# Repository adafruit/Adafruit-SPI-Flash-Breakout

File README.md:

## Adafruit SPI Flash Breakouts

&nbsp; 
<br />
&nbsp; 

Click to purchase from the Adafruit Shop:
- [Adafruit SPI FLASH Breakout - W25Q16 - 16 Mbit / 2 MByte](https://www.adafruit.com/product/5635)
- [Adafruit SPI FLASH Breakout - W25Q64 - 64 MBit / 8 MByte](https://www.adafruit.com/product/5636)
- [Adafruit SPI FLASH Breakout W25Q128 - 128 MBit / 16 MByte](https://www.adafruit.com/product/5643)

PCB files for the Adafruit SPI Flash Breakouts. 

Format is EagleCAD schematic and board layout

### Description

Sometimes you need a little extra storage for your microcontroller projects: for files, images, fonts, audio clips, etc. If you need lots of space, like in the gigabytes, we always recommend an SD card because you can easily plug it into a computer to edit files. But sometimes you don't need whole gigabytes, you just need a megabyte or two, with the lower cost and power usage that comes with it. That's when we recommend an Adafruit SPI FLASH Breakout such as this one that is fitted with a W25Q16 - 16 Mbit / 2 MByte, W25Q64 - 64 Mbit / 8 MByte or W25Q128 - 128 Mbit / 16 MByte chip.

Compared to our QSPI breakouts, this one is single-channel SPI only...BUT it comes with level shifting so it can be used safely with 3V or 5V power and logic. Since we needed to add level shifting, the chip is pre-wired into single channel "SPI" mode, with a level shifters so you can use it with 3V or 5V logic easily. You also get a 3.3V regulator and a pullup on CS. 

Note that the chips come blank, and do not have a wear-leveling subsystem. You can address them as a flat memory space or, if you like, format them with a filesystem like littleFS or FAT. Great for use with data-logging or storage needs where you are OK with doing the management yourself - or if you are adding external memory to an older chip that would like 5V-compatibility.

In Arduino, we have the Adafruit_SPIFlash library that can be used to interface with this chip. Comes with a bit of header that can be used to solder in and plug into a breadboard if desired.

### License

Adafruit invests time and resources providing this open source design, please support Adafruit and open-source hardware by purchasing products from [Adafruit](https://www.adafruit.com)!

Designed by Limor Fried/Ladyada for Adafruit Industries.

Creative Commons Attribution/Share-Alike, all text above must be included in any redistribution. 
See license.txt for additional details.

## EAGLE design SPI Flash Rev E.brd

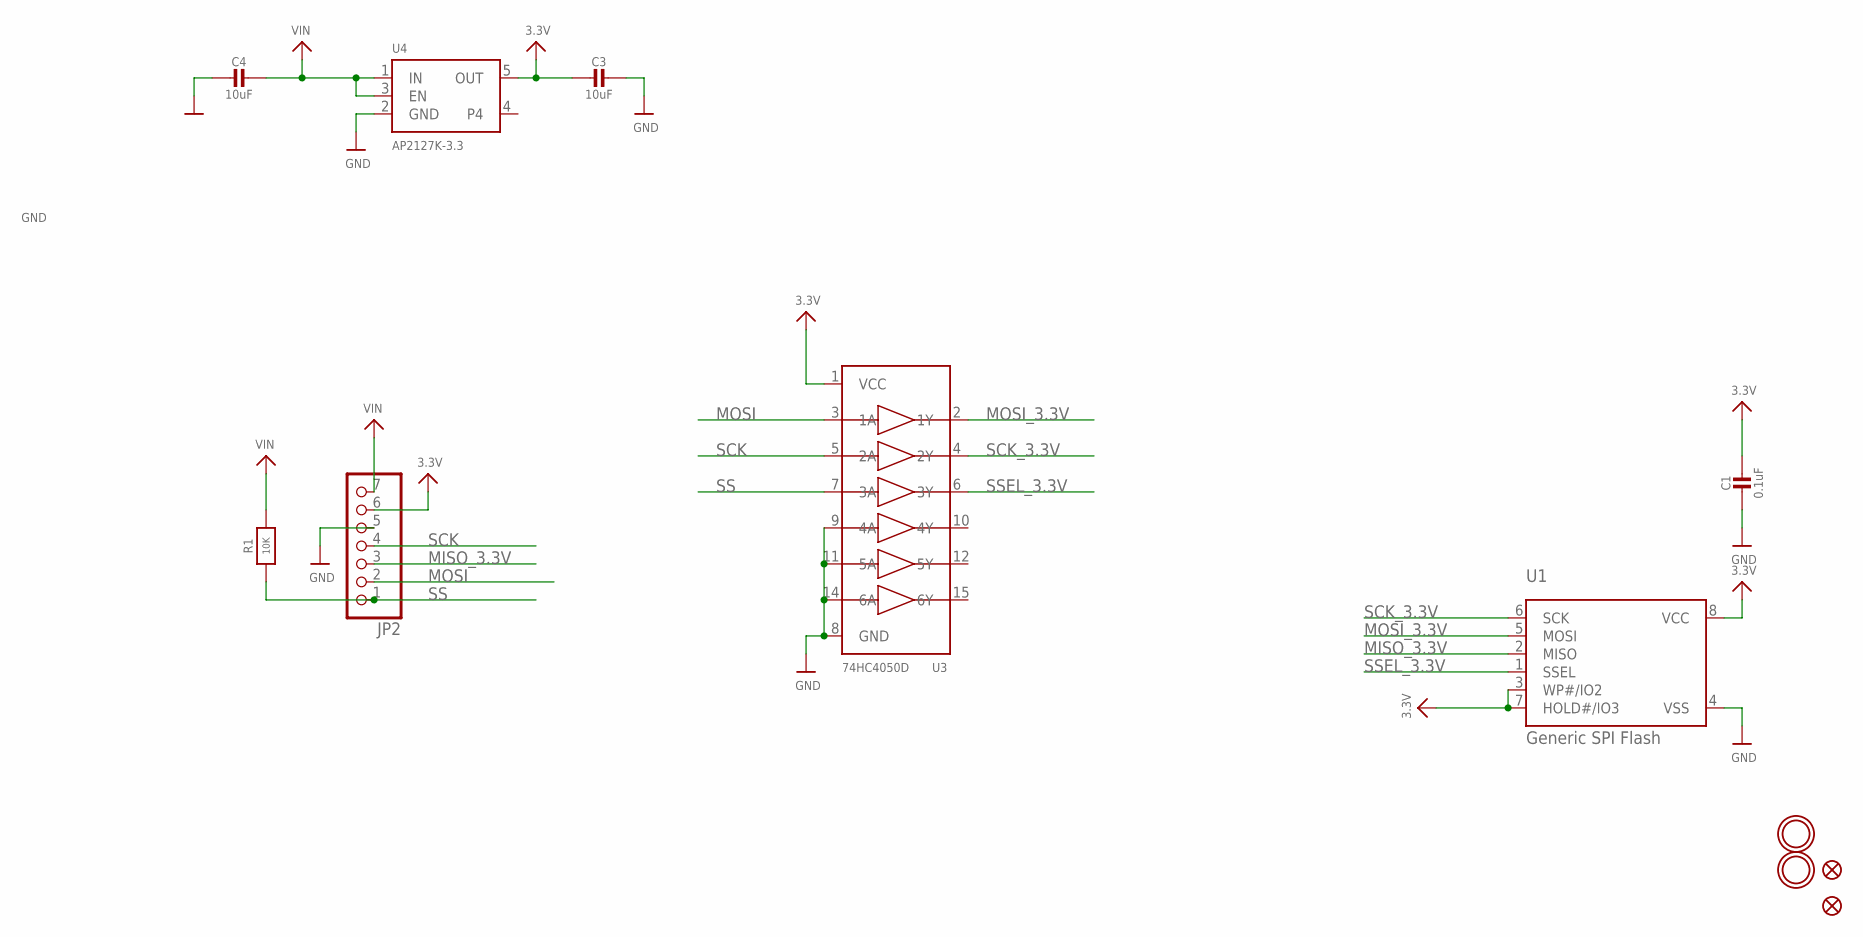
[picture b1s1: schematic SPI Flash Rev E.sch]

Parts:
C1: 0.1uF; 0603-NO
C3, C4: 10uF; 0805-NO
FID2, FID3: FIDUCIAL_1MM
JP2: HEADER-1X770MIL; 1X07_ROUND_70
R1: 10K; 0603-NO
U1: Generic SPI Flash; SOIC8_208MIL
U3: 74HC4050D; TSSOP16
U4: AP2127K-3.3; SOT23-5
U$16, U$17: MOUNTINGHOLE2.5; MOUNTINGHOLE_2.5_PLATED

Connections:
3.3V: C1.1, C3.2, JP2.6, U1.3 (WP#/IO2), U1.7 (HOLD#/IO3), U1.8 (VCC), U3.1 (VCC), U4.5 (OUT)
GND: C1.2, C3.1, C4.2, JP2.5, U1.4 (VSS), U3.8 (GND), U3.9 (4A), U3.11 (5A), U3.14 (6A), U4.2 (GND)
MISO_3.3V: JP2.3, U1.2 (MISO)
MOSI: JP2.2, U3.3 (1A)
MOSI_3.3V: U1.5 (MOSI), U3.2 (1Y)
SCK: JP2.4, U3.5 (2A)
SCK_3.3V: U1.6 (SCK), U3.4 (2Y)
SS: JP2.1, R1.1, U3.7 (3A)
SSEL_3.3V: U1.1 (SSEL), U3.6 (3Y)
VIN: C4.1, JP2.7, R1.2, U4.1 (IN), U4.3 (EN)

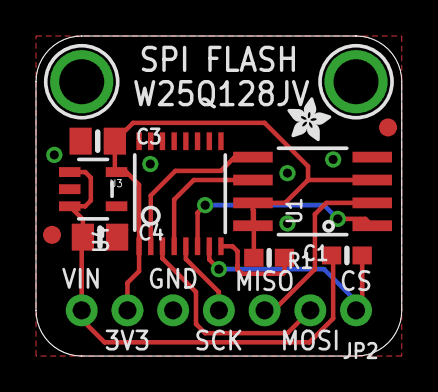
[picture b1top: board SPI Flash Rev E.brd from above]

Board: 2 copper layers, 20.3 x 17.8 mm, 14 parts (1 on the bottom side), 10 nets.

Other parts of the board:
U$13: ADAFRUIT_2.5MM
U$21: PCBFEAT-REV-040

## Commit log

2022-11-14 adding cookiecutter output

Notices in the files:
parts and their libraries:
microbuilder: This work is placed in the public domain, and may be freely used for commercial and non-commercial work with the following conditions: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
